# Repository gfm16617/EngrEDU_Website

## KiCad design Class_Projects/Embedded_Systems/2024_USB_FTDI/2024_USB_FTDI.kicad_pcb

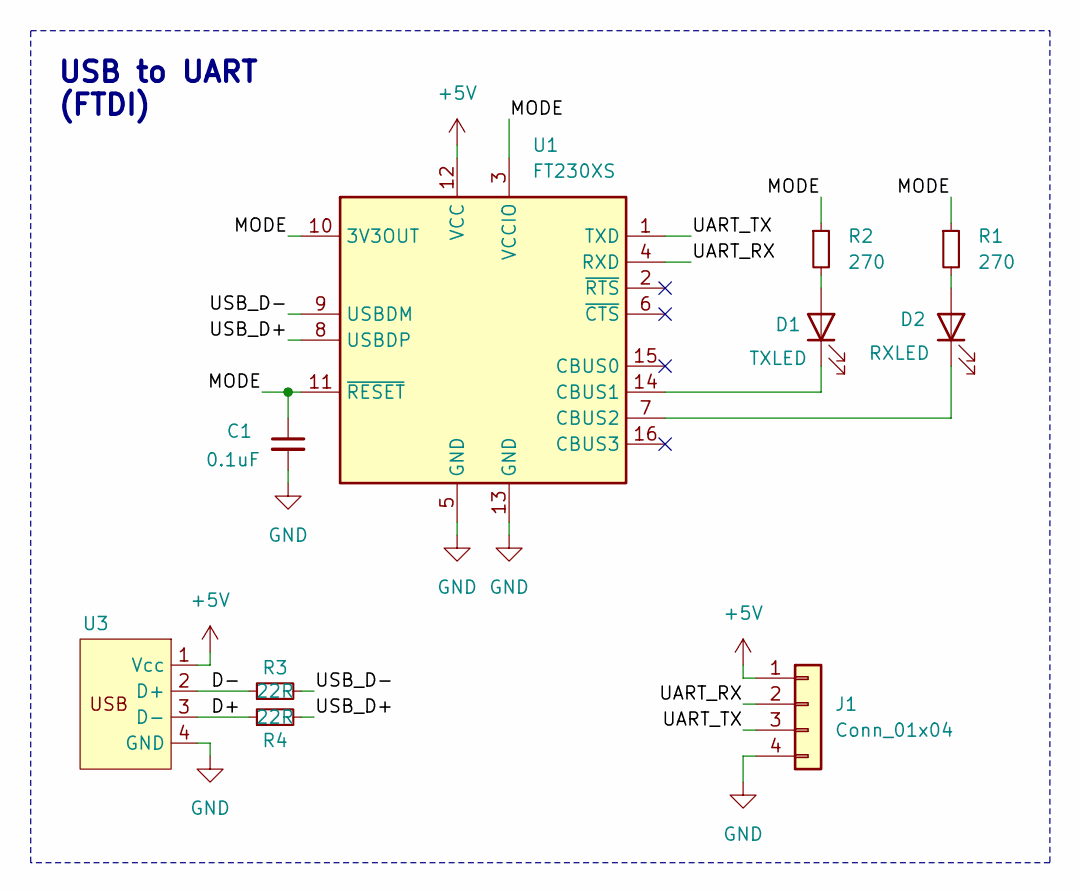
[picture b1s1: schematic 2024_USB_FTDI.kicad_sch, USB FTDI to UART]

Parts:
C1: 0.1uF; C_0805_2012Metric_Pad1.18x1.45mm_HandSolder
D1: TXLED; LED_0805_2012Metric_Pad1.15x1.40mm_HandSolder
D2: RXLED; LED_0805_2012Metric_Pad1.15x1.40mm_HandSolder
J1: Conn_01x04; PinHeader_1x04_P2.54mm_Vertical
R1, R2: 270; R_0805_2012Metric_Pad1.20x1.40mm_HandSolder
R3, R4: 22R; R_0805_2012Metric_Pad1.20x1.40mm_HandSolder
U1: FT230XS; SSOP-16_3.9x4.9mm_P0.635mm
U3: USB_PCB_Connector_SMD

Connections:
+5V: J1.1, U1.12 (VCC), U3.1 (Vcc)
/D+: R4.1, U3.3 (D-)
/D-: R3.1, U3.2 (D+)
/MODE: C1.1, R1.1, R2.1, U1.3 (VCCIO), U1.10 (3V3OUT), U1.11 (~RESET)
/UART_RX: J1.2, U1.4 (RXD)
/UART_TX: J1.3, U1.1 (TXD)
/USB_D+: R4.2, U1.8 (USBDP)
/USB_D-: R3.2, U1.9 (USBDM)
GND: C1.2, J1.4, U1.5 (GND), U1.13 (GND), U3.4 (GND)
unnamed: D1.2 (A), R2.2
unnamed: D1.1 (K), U1.14 (CBUS1)
unnamed: D2.2 (A), R1.2
unnamed: D2.1 (K), U1.7 (CBUS2)

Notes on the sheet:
USB to UART (FTDI)

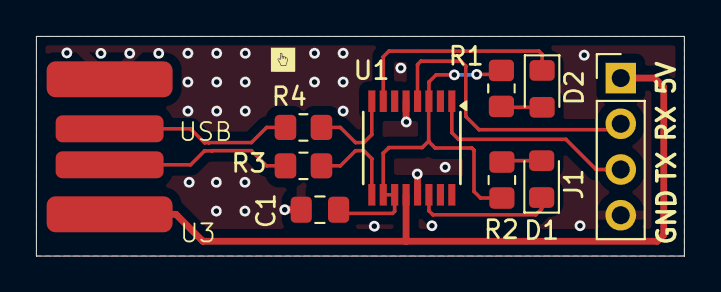
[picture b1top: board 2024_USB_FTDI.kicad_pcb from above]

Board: 2 copper layers, 36.0 x 12.2 mm, 10 parts (0 on the bottom side), 13 nets.

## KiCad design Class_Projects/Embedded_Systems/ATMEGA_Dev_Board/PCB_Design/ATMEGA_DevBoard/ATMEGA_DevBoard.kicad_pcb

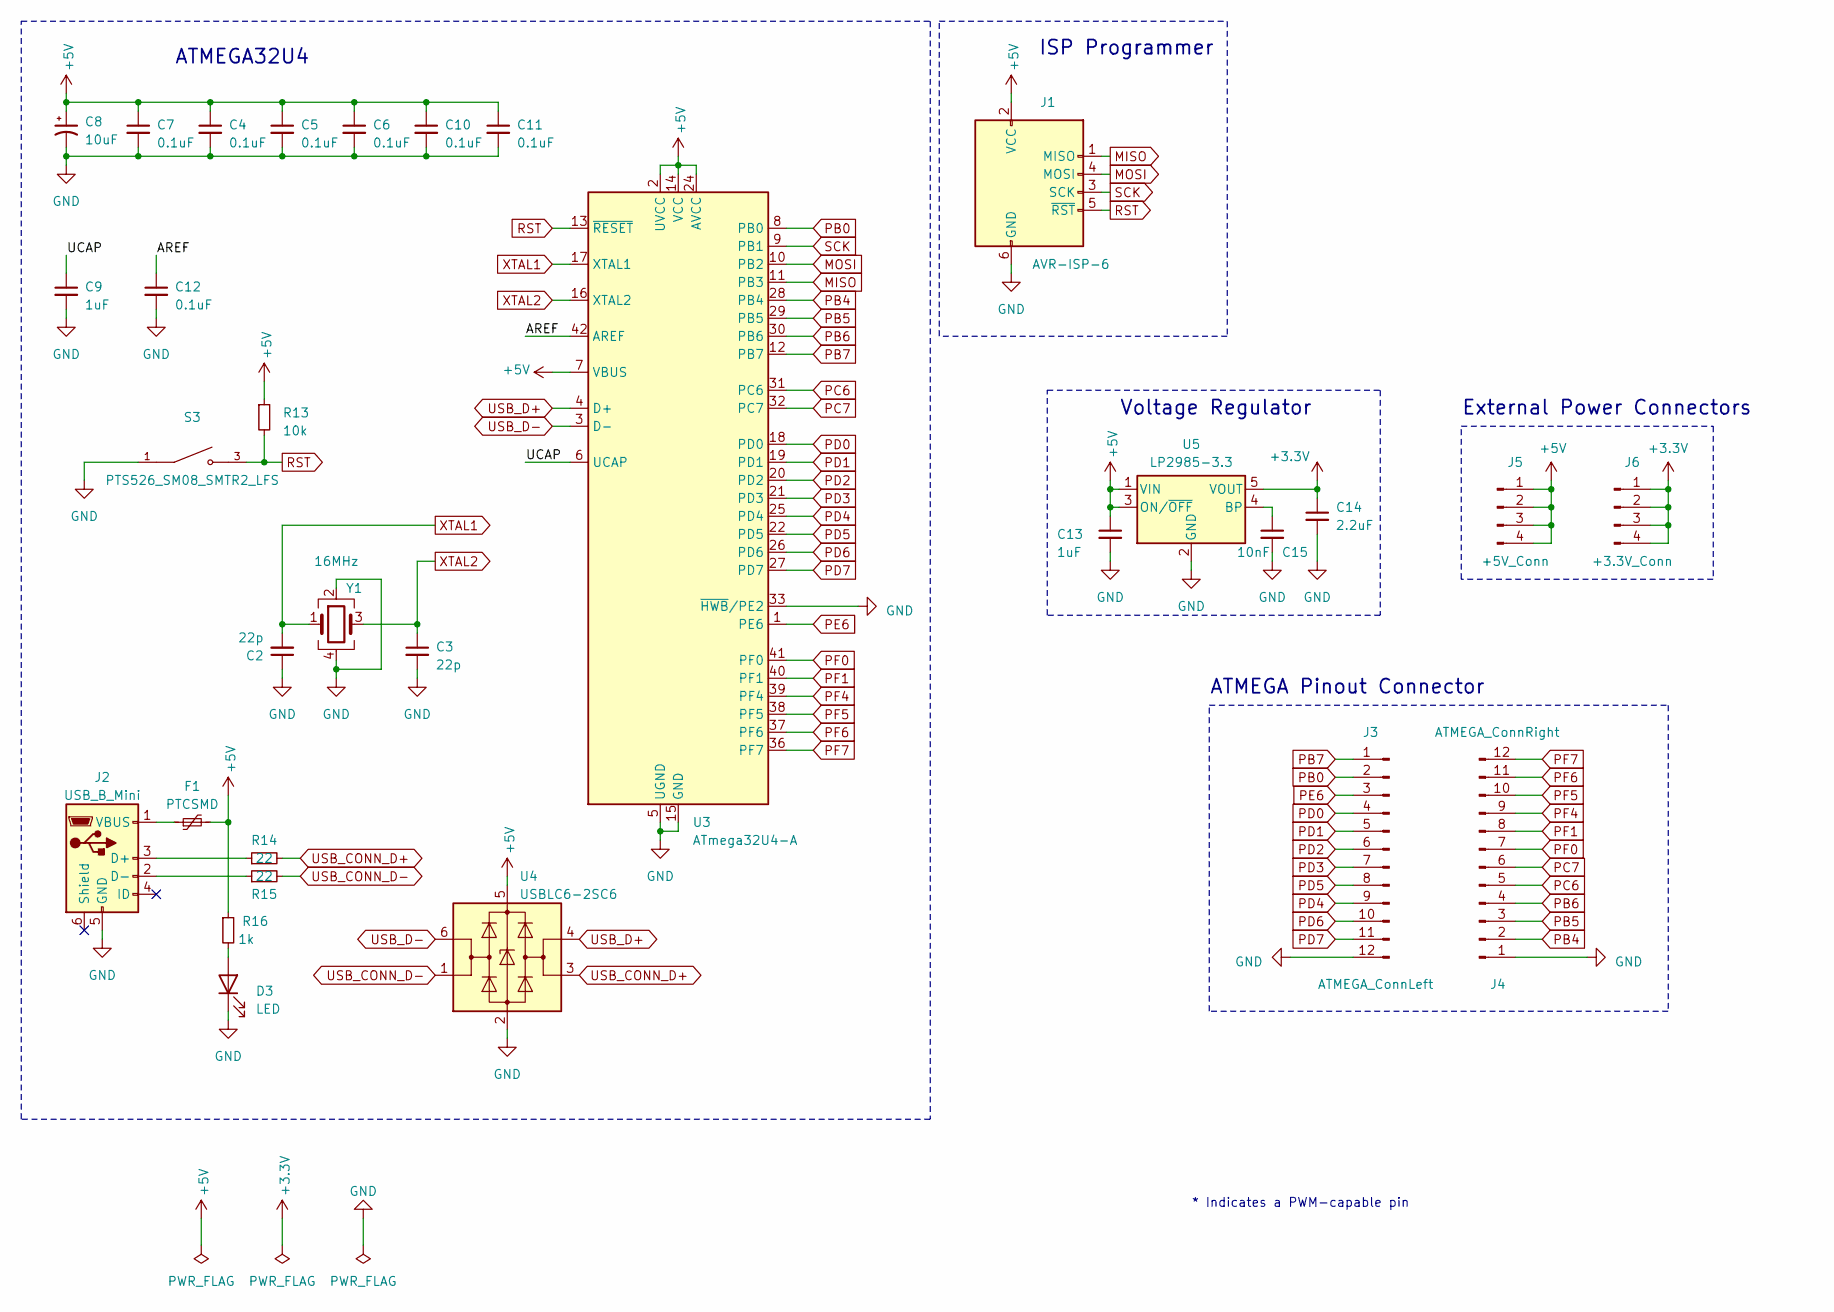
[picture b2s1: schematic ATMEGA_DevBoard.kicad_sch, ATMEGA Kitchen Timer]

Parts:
C2, C3: 22p; C_0603_1608Metric
C4, C5, C6, C7, C10, C11, C12: 0.1uF; C_0603_1608Metric
C8: 10uF; C_0805_2012Metric
C9, C13: 1uF; C_0603_1608Metric
C14: 2.2uF; C_0603_1608Metric
C15: 10nF; C_0603_1608Metric
D3: LED; LED_0805_2012Metric
F1: PTCSMD; Fuse_1812_4532Metric
J1: AVR-ISP-6; PinSocket_2x03_P2.54mm_Vertical
J2: USB_B_Mini; USB_Mini-B_Lumberg_2486_01_Horizontal
J3: ATMEGA_ConnLeft; PinHeader_1x12_P2.54mm_Vertical
J4: ATMEGA_ConnRight; PinHeader_1x12_P2.54mm_Vertical
J5: +5V_Conn; PinHeader_1x04_P2.54mm_Vertical
J6: +3.3V_Conn; PinHeader_1x04_P2.54mm_Vertical
R13: 10k; R_0603_1608Metric
R14, R15: 22; R_0603_1608Metric
R16: 1k; R_0603_1608Metric
S3: PTS526_SM08_SMTR2_LFS; PTS526_SMD_Button; PARTREV 20 mar 19
U3: ATmega32U4-A; TQFP-44_10x10mm_P0.8mm
U4: USBLC6-2SC6; SOT-23-6
U5: LP2985-3.3; SOT-23-5
Y1: 16MHz; Crystal_SMD_Abracon_ABM8G-4Pin_3.2x2.5mm

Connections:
+3.3V: C14.1, J6.1, J6.2, J6.3, J6.4, U5.5 (VOUT)
+5V: C4.1, C5.1, C6.1, C7.1, C8.1, C10.1, C11.1, C13.1, F1.2, J1.2 (VCC), J5.1, J5.2, J5.3, J5.4, R13.1, R16.1, U3.2 (UVCC), U3.7 (VBUS), U3.14 (VCC), U3.24 (AVCC), U3.34 (VCC), U3.44 (AVCC), U4.5 (VBUS), U5.1 (VIN), U5.3 (ON/~OFF)
/AREF: C12.1, U3.42 (AREF)
/UCAP: C9.1, U3.6 (UCAP)
GND: C2.1, C3.2, C4.2, C5.2, C6.2, C7.2, C8.2, C9.2, C10.2, C11.2, C12.2, C13.2, C14.2, C15.2, D3.1 (K), J1.6 (GND), J2.5 (GND), J3.12, J4.1, S3.1, U3.5 (UGND), U3.15 (GND), U3.23 (GND), U3.33 (~HWB/PE2), U3.35 (GND), U3.43 (GND), U4.2 (GND), U5.2 (GND), Y1.2, Y1.4
MISO: J1.1 (MISO), U3.11 (PB3)
MOSI: J1.4 (MOSI), U3.10 (PB2)
unnamed: D3.2 (A), R16.2
unnamed: J2.3 (D+), R14.1
unnamed: J2.2 (D-), R15.1
unnamed: F1.1, J2.1 (VBUS)
unnamed: C15.1, U5.4 (BP)
PB0: J3.2, U3.8 (PB0)
PB4: J4.2, U3.28 (PB4)
PB5: J4.3, U3.29 (PB5)
PB6: J4.4, U3.30 (PB6)
PB7: J3.1, U3.12 (PB7)
PC6: J4.5, U3.31 (PC6)
PC7: J4.6, U3.32 (PC7)
PD0: J3.4, U3.18 (PD0)
PD1: J3.5, U3.19 (PD1)
PD2: J3.6, U3.20 (PD2)
PD3: J3.7, U3.21 (PD3)
PD4: J3.9, U3.25 (PD4)
PD5: J3.8, U3.22 (PD5)
PD6: J3.10, U3.26 (PD6)
PD7: J3.11, U3.27 (PD7)
PE6: J3.3, U3.1 (PE6)
PF0: J4.7, U3.41 (PF0)
PF1: J4.8, U3.40 (PF1)
PF4: J4.9, U3.39 (PF4)
PF5: J4.10, U3.38 (PF5)
PF6: J4.11, U3.37 (PF6)
PF7: J4.12, U3.36 (PF7)
RST: J1.5 (~RST), R13.2, S3.3, U3.13 (~RESET)
SCK: J1.3 (SCK), U3.9 (PB1)
USB_CONN_D+: R14.2, U4.3 (I/O2)
USB_CONN_D-: R15.2, U4.1 (I/O1)
USB_D+: U3.4 (D+), U4.4 (I/O2)
USB_D-: U3.3 (D-), U4.6 (I/O1)
XTAL1: C2.2, U3.17 (XTAL1), Y1.1
XTAL2: C3.1, U3.16 (XTAL2), Y1.3

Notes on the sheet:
External Power Connectors
Voltage Regulator
ATMEGA32U4
* Indicates a PWM-capable pin
ISP Programmer
ATMEGA Pinout Connector

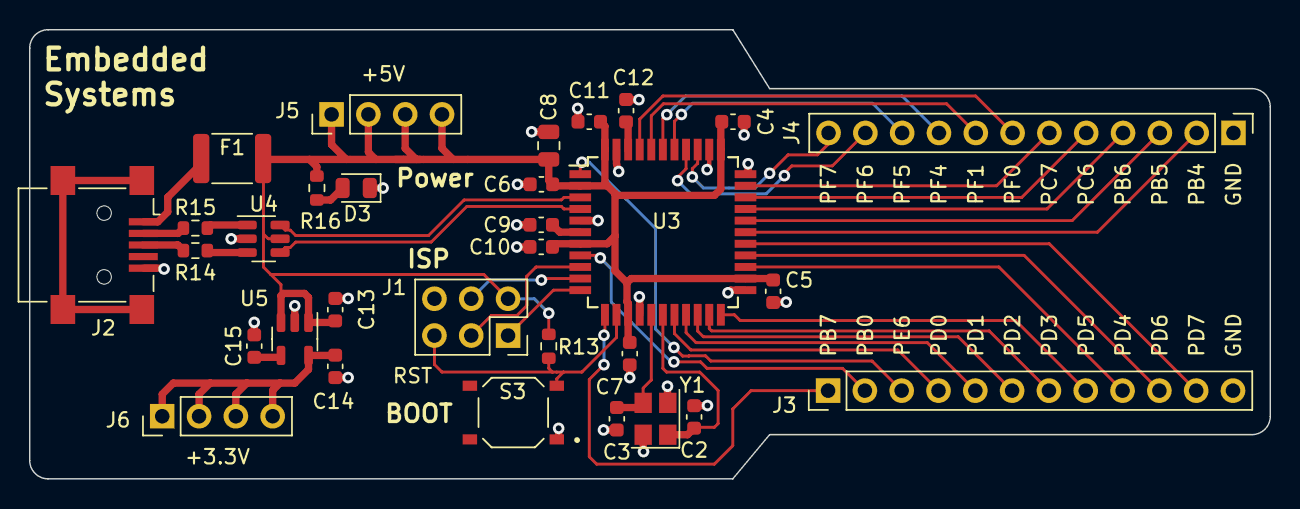
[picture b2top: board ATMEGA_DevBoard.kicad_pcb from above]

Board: 2 copper layers, 85.6 x 31.0 mm, 31 parts (0 on the bottom side), 42 nets.

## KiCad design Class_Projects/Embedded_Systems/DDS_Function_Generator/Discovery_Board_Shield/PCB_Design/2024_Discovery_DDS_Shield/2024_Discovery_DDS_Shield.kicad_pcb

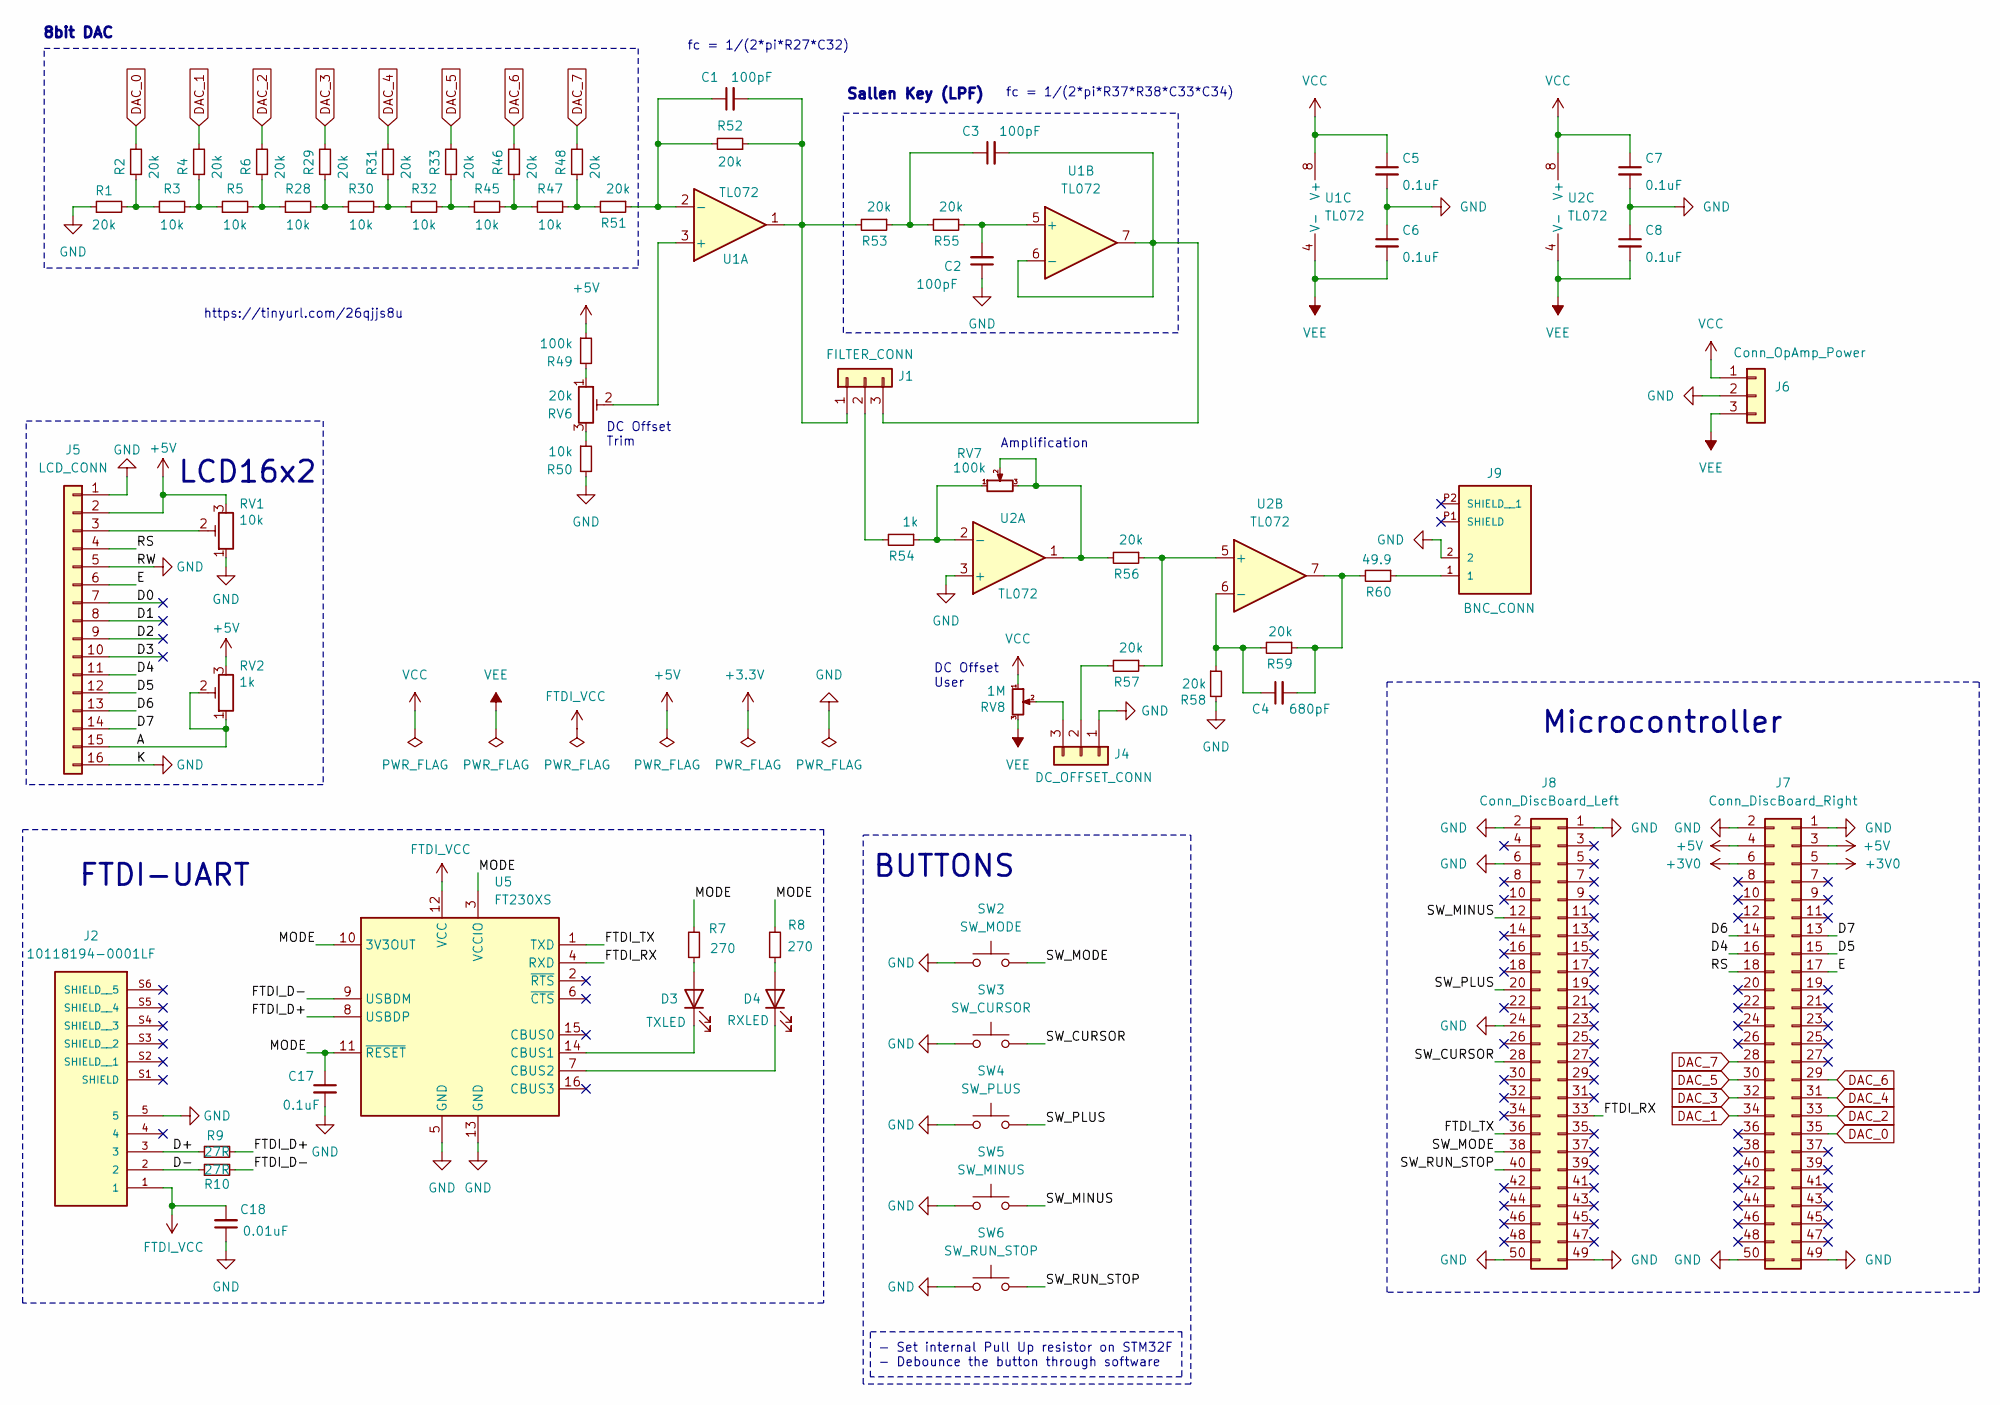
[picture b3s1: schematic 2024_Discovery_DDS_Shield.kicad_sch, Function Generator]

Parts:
C1, C2, C3: 100pF; C_0805_2012Metric_Pad1.18x1.45mm_HandSolder
C4: 680pF; C_0805_2012Metric_Pad1.18x1.45mm_HandSolder
C5, C6, C7, C8, C17: 0.1uF; C_0805_2012Metric_Pad1.18x1.45mm_HandSolder
C18: 0.01uF; C_0805_2012Metric_Pad1.18x1.45mm_HandSolder
D3: TXLED; LED_0805_2012Metric_Pad1.15x1.40mm_HandSolder
D4: RXLED; LED_0805_2012Metric_Pad1.15x1.40mm_HandSolder
J1: FILTER_CONN; PinSocket_1x03_P2.54mm_Vertical
J2: 10118194-0001LF; AMPHENOL_10118194-0001LF; PARTREV D
J4: DC_OFFSET_CONN; PinSocket_1x03_P2.54mm_Vertical
J5: LCD_CONN; PinSocket_1x16_P2.54mm_Vertical
J6: Conn_OpAmp_Power; PinHeader_1x03_P2.54mm_Vertical
J7: Conn_DiscBoard_Right; PinSocket_2x25_P2.54mm_Vertical
J8: Conn_DiscBoard_Left; PinSocket_2x25_P2.54mm_Vertical
J9: BNC_CONN; BNC_RightAngle_50ohm
R1, R2, R4, R6, R29, R31, R33, R46, R48, R51, R52, R53, R55, R56, R57, R58, R59: 20k; R_0805_2012Metric_Pad1.20x1.40mm_HandSolder
R3, R5, R28, R30, R32, R45, R47, R50: 10k; R_0805_2012Metric_Pad1.20x1.40mm_HandSolder
R7, R8: 270; R_0805_2012Metric_Pad1.20x1.40mm_HandSolder
R9, R10: 27R; R_0805_2012Metric_Pad1.20x1.40mm_HandSolder
R49: 100k; R_0805_2012Metric_Pad1.20x1.40mm_HandSolder
R54: 1k; R_0805_2012Metric_Pad1.20x1.40mm_HandSolder
R60: 49.9; R_0805_2012Metric_Pad1.20x1.40mm_HandSolder
RV1: 10k; Potentiometer_Bourns_3296W_Vertical
RV2: 1k; Potentiometer_Bourns_3296W_Vertical
RV6: 20k; Potentiometer_Bourns_3296W_Vertical
RV7: 100k; Potentiometer_Alps_RK09K_Single_Vertical
RV8: 1M; Potentiometer_Alps_RK09K_Single_Vertical
SW2: SW_MODE; SW_PUSH_6mm_H5mm
SW3: SW_CURSOR; SW_PUSH_6mm_H5mm
SW4: SW_PLUS; SW_PUSH_6mm_H5mm
SW5: SW_MINUS; SW_PUSH_6mm_H5mm
SW6: SW_RUN_STOP; SW_PUSH_6mm_H5mm
U1, U2: TL072; SOIC-8_3.9x4.9mm_P1.27mm
U5: FT230XS; SSOP-16_3.9x4.9mm_P0.635mm

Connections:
+3V0: J7.5, J7.6
+5V: J5.2, J7.3, J7.4, R49.1, RV1.3, RV2.3
/A: J5.15, RV2.1, RV2.2
/D0: J5.7
/D1: J5.8
/D2: J5.9
/D3: J5.10
/D4: J5.11, J7.16
/D5: J5.12, J7.15
/D6: J5.13, J7.14
/D7: J5.14, J7.13
/D+: J2.3, R9.1
/D-: J2.2, R10.1
/E: J5.6, J7.17
/FTDI_D+: R9.2, U5.8 (USBDP)
/FTDI_D-: R10.2, U5.9 (USBDM)
/FTDI_RX: J8.33, U5.4 (RXD)
/FTDI_TX: J8.36, U5.1 (TXD)
/MODE: C17.1, R7.2, R8.2, U5.3 (VCCIO), U5.10 (3V3OUT), U5.11 (~RESET)
/RS: J5.4, J7.18
/SW_CURSOR: J8.28, SW3.2
/SW_MINUS: J8.12, SW5.2
/SW_MODE: J8.38, SW2.2
/SW_PLUS: J8.20, SW4.2
/SW_RUN_STOP: J8.40, SW6.2
DAC_0: J7.35, R2.2
DAC_1: J7.34, R4.2
DAC_2: J7.33, R6.2
DAC_3: J7.32, R29.2
DAC_4: J7.31, R31.2
DAC_5: J7.30, R33.2
DAC_6: J7.29, R46.2
DAC_7: J7.28, R48.2
FTDI_VCC: C18.2, J2.1, U5.12 (VCC)
GND: C2.1, C5.2, C6.1, C7.2, C8.1, C17.2, C18.1, J2.5, J4.1, J5.1, J5.5, J5.16, J6.2, J7.1, J7.2, J7.49, J7.50, J8.1, J8.2, J8.6, J8.24, J8.49, J8.50, J9.2, R1.1, R50.2, R58.2, RV1.1, SW2.1, SW3.1, SW4.1, SW5.1, SW6.1, U2.3 (+), U5.5 (GND), U5.13 (GND)
unnamed: C3.1, R53.1, R55.2
unnamed: C4.2, R59.1, R60.2, U2.7
unnamed: D3.2 (A), R7.1
unnamed: D3.1 (K), U5.14 (CBUS1)
unnamed: D4.2 (A), R8.1
unnamed: D4.1 (K), U5.7 (CBUS2)
unnamed: C1.2, J1.1, R52.1, R53.2, U1.1
unnamed: J1.2, R54.2
unnamed: C3.2, J1.3, U1.6 (-), U1.7
unnamed: J4.2, R57.2
unnamed: J4.3, RV8.2
unnamed: J5.3, RV1.2
unnamed: J9.1, R60.1
unnamed: R1.2, R2.1, R3.1
unnamed: R3.2, R4.1, R5.1
unnamed: R5.2, R6.1, R28.1
unnamed: R28.2, R29.1, R30.1
unnamed: R30.2, R31.1, R32.1
unnamed: R32.2, R33.1, R45.1
unnamed: R45.2, R46.1, R47.2
unnamed: R47.1, R48.1, R51.2
unnamed: R49.2, RV6.1
unnamed: R50.1, RV6.3
unnamed: R56.2, RV7.2, RV7.3, U2.1
unnamed: RV6.2, U1.3 (+)
unnamed: C1.1, R51.1, R52.2, U1.2 (-)
unnamed: C2.2, R55.1, U1.5 (+)
unnamed: R54.1, RV7.1, U2.2 (-)
unnamed: R56.1, R57.1, U2.5 (+)
unnamed: C4.1, R58.1, R59.2, U2.6 (-)
VCC: C5.1, C7.1, J6.1, RV8.1, U1.8 (V+), U2.8 (V+)
VEE: C6.2, C8.2, J6.3, RV8.3, U1.4 (V-), U2.4 (V-)

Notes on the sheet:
- Set internal Pull Up resistor on STM32F - Debounce the button through software
Microcontroller
fc = 1/(2*pi*R37*R38*C33*C34)
BUTTONS
fc = 1/(2*pi*R27*C32)
8bit DAC
https://tinyurl.com/26qjjs8u
Amplification
DC Offset Trim
DC Offset User
LCD16x2
Sallen Key (LPF)
FTDI-UART

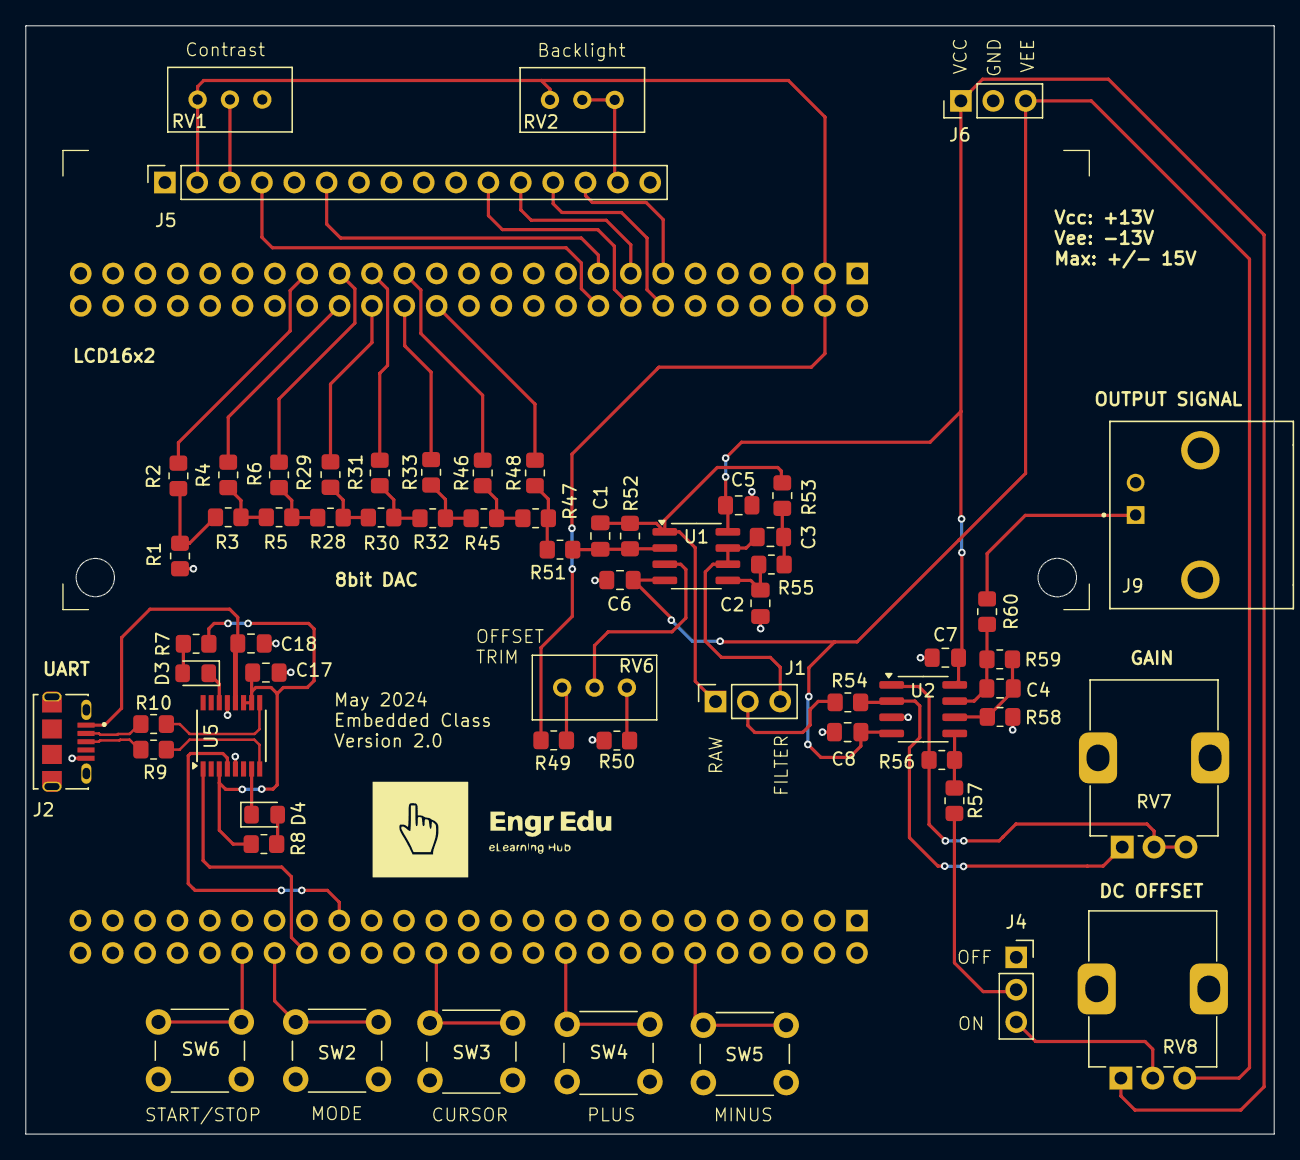
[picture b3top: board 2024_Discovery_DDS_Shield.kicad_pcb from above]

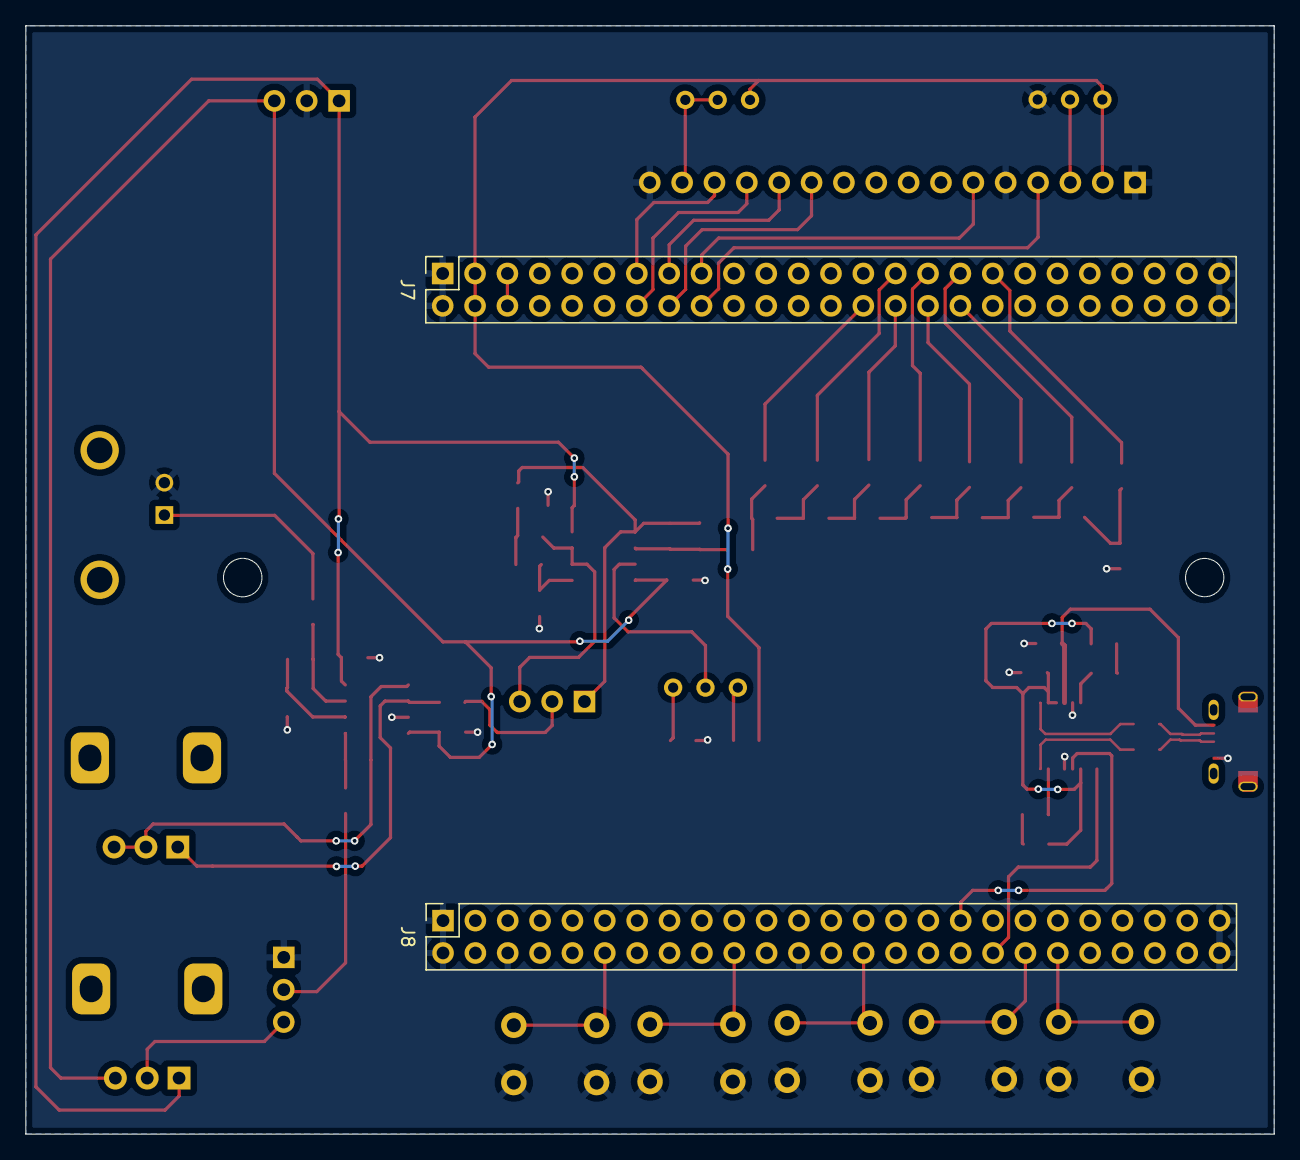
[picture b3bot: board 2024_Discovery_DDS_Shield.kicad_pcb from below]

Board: 2 copper layers, 98.0 x 87.0 mm, 65 parts (2 on the bottom side), 63 nets.

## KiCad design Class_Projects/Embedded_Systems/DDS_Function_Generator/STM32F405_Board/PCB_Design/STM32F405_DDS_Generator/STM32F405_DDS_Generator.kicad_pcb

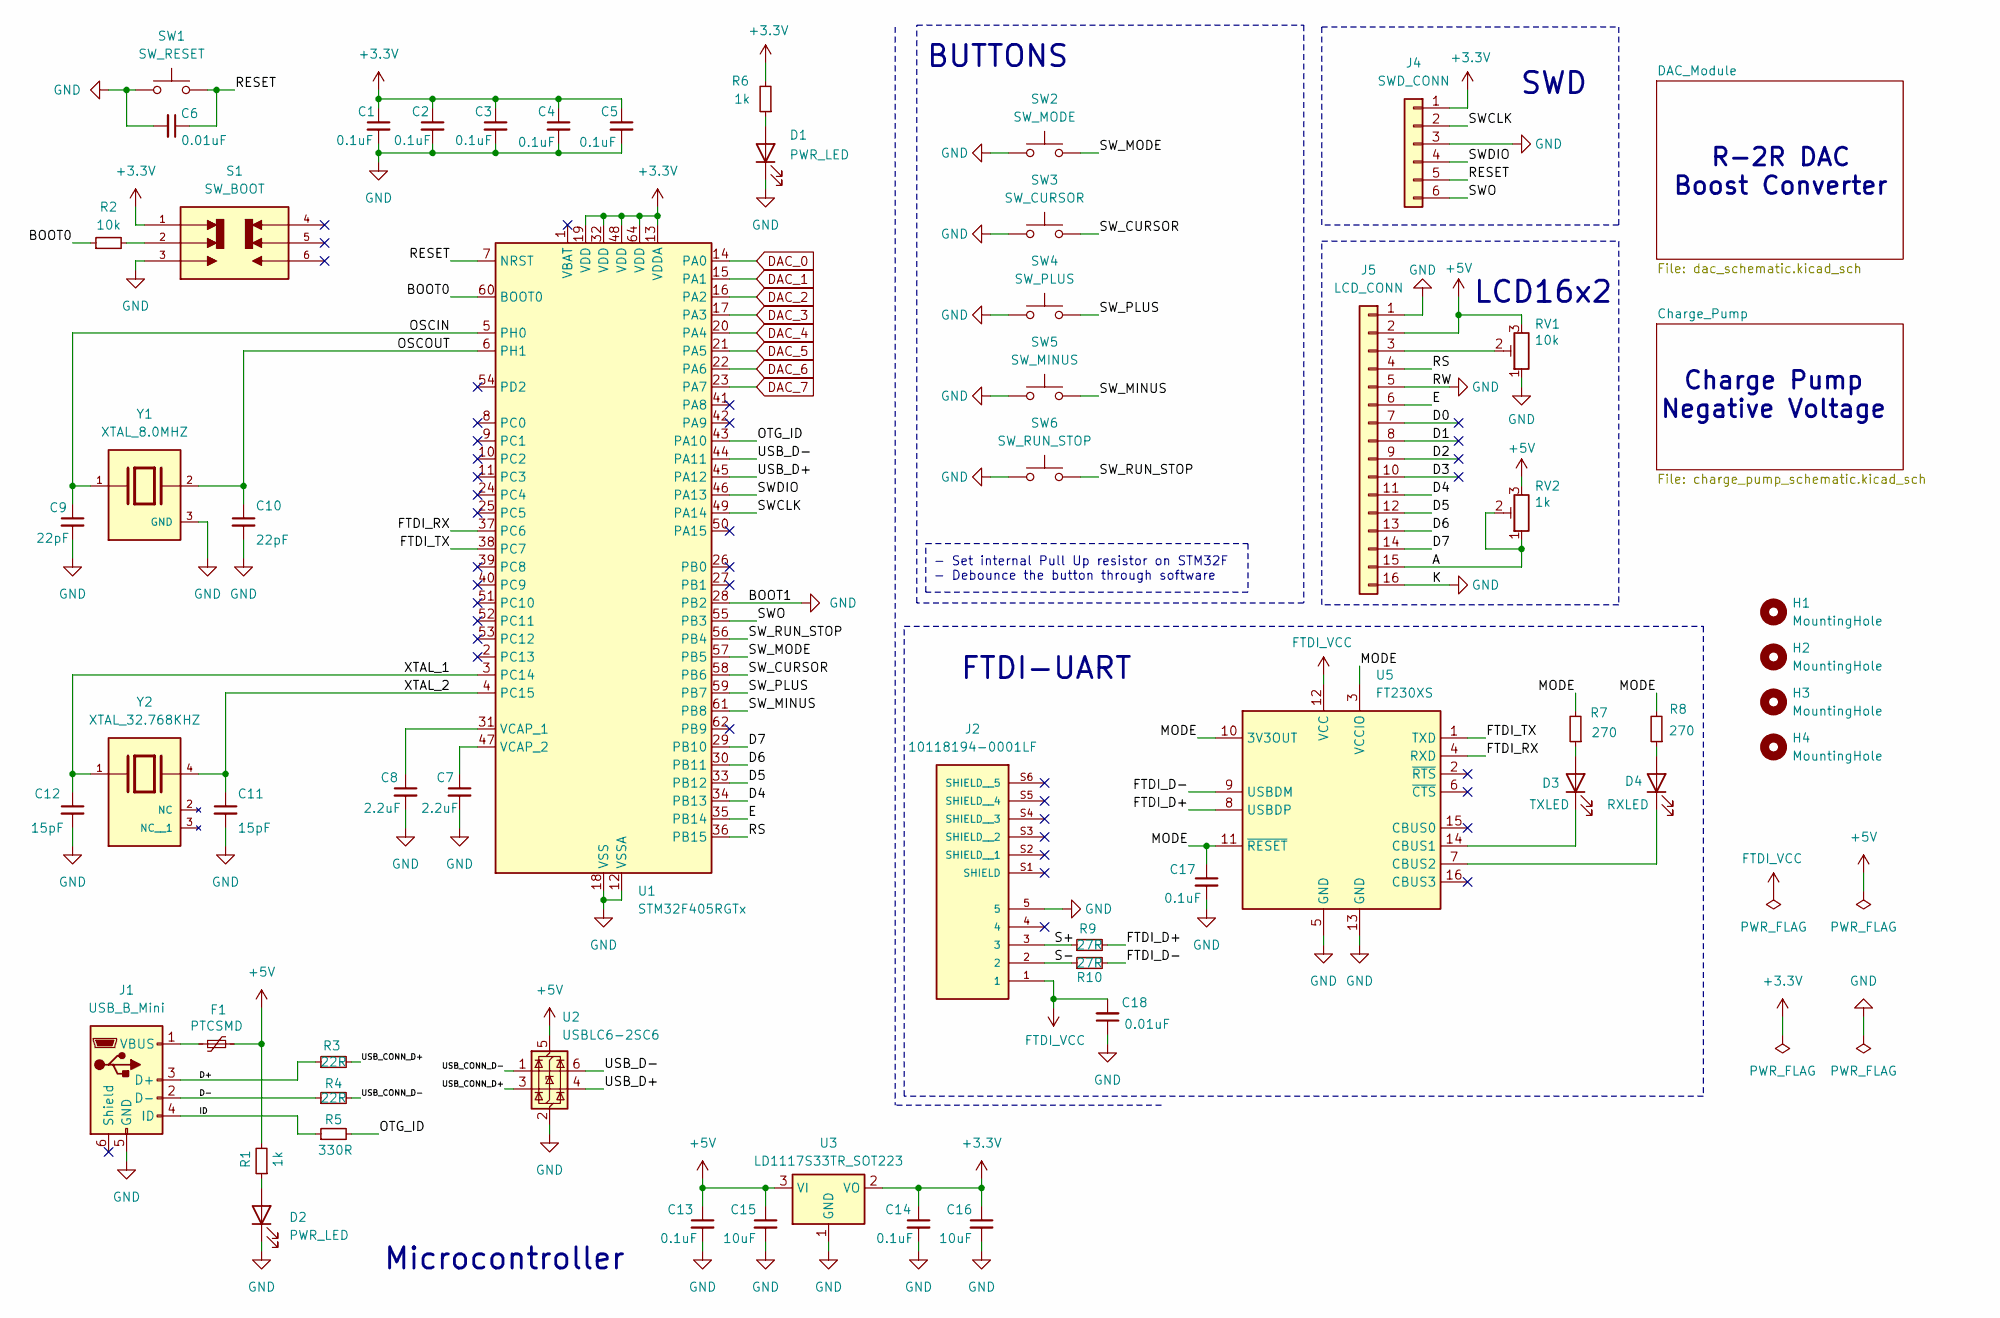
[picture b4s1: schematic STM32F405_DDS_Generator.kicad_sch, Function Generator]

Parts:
C1, C2, C3, C4, C5, C13, C14, C17: 0.1uF; C_0805_2012Metric_Pad1.18x1.45mm_HandSolder
C6, C18: 0.01uF; C_0805_2012Metric_Pad1.18x1.45mm_HandSolder
C7, C8: 2.2uF; C_0805_2012Metric_Pad1.18x1.45mm_HandSolder
C9, C10: 22pF; C_0805_2012Metric_Pad1.18x1.45mm_HandSolder
C11, C12: 15pF; C_0805_2012Metric_Pad1.18x1.45mm_HandSolder
C15, C16: 10uF; C_0805_2012Metric_Pad1.18x1.45mm_HandSolder
D1, D2: PWR_LED; LED_0805_2012Metric_Pad1.15x1.40mm_HandSolder
D3: TXLED; LED_0805_2012Metric_Pad1.15x1.40mm_HandSolder
D4: RXLED; LED_0805_2012Metric_Pad1.15x1.40mm_HandSolder
F1: PTCSMD; Fuse_1812_4532Metric
H1, H2, H3, H4: MountingHole; MountingHole_3.2mm_M3_Pad_Via
J1: USB_B_Mini; USB_Mini-B_Wuerth_65100516121_Horizontal
J2: 10118194-0001LF; AMPHENOL_10118194-0001LF; PARTREV D
J4: SWD_CONN; PinHeader_1x06_P2.54mm_Vertical
J5: LCD_CONN; PinSocket_1x16_P2.54mm_Vertical
R1, R6: 1k; R_0805_2012Metric_Pad1.20x1.40mm_HandSolder
R2: 10k; R_0805_2012Metric_Pad1.20x1.40mm_HandSolder
R3, R4: 22R; R_0805_2012Metric_Pad1.20x1.40mm_HandSolder
R5: 330R; R_0805_2012Metric_Pad1.20x1.40mm_HandSolder
R7, R8: 270; R_0805_2012Metric_Pad1.20x1.40mm_HandSolder
R9, R10: 27R; R_0805_2012Metric_Pad1.20x1.40mm_HandSolder
RV1: 10k; Potentiometer_Bourns_3296W_Vertical
RV2: 1k; Potentiometer_Bourns_3296W_Vertical
S1: SW_BOOT; SW_JS202011SCQN; PARTREV 26 May 22
SW1: SW_RESET; PTS636SM25FSMTRLFS
SW2: SW_MODE; SW_PUSH_6mm_H5mm
SW3: SW_CURSOR; SW_PUSH_6mm_H5mm
SW4: SW_PLUS; SW_PUSH_6mm_H5mm
SW5: SW_MINUS; SW_PUSH_6mm_H5mm
SW6: SW_RUN_STOP; SW_PUSH_6mm_H5mm
U1: STM32F405RGTx; LQFP-64_10x10mm_P0.5mm
U2: USBLC6-2SC6; SOT-23-6
U3: LD1117S33TR_SOT223; SOT-223-3_TabPin2
U5: FT230XS; SSOP-16_3.9x4.9mm_P0.635mm
Y1: XTAL_8.0MHZ; XTAL_ABLSG-8.000MHZ-D-2-Y-T; PARTREV 08.20.10
Y2: XTAL_32.768KHZ; XTAL_ABS25-32.768KHZ-1-T; PARTREV 43738

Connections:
+3.3V: C1.1, C2.1, C3.1, C4.1, C5.1, C14.1, C16.1, J4.1, R6.2, S1.1, U1.13 (VDDA), U1.19 (VDD), U1.32 (VDD), U1.48 (VDD), U1.64 (VDD), U3.2 (VO)
+5V: C13.1, C15.1, F1.2, J5.2, R1.2, RV1.3, RV2.3, U2.5 (VBUS), U3.3 (VI); also elsewhere on the board
/A: J5.15, RV2.1, RV2.2
/BOOT0: R2.1, U1.60 (BOOT0)
/D0: J5.7
/D1: J5.8
/D2: J5.9
/D3: J5.10
/D4: J5.11, U1.34 (PB13)
/D5: J5.12, U1.33 (PB12)
/D6: J5.13, U1.30 (PB11)
/D7: J5.14, U1.29 (PB10)
/D+: J1.3 (D+), R3.1
/D-: J1.2 (D-), R4.1
/E: J5.6, U1.35 (PB14)
/FTDI_D+: R9.2, U5.8 (USBDP)
/FTDI_D-: R10.2, U5.9 (USBDM)
/FTDI_RX: U1.37 (PC6), U5.4 (RXD)
/FTDI_TX: U1.38 (PC7), U5.1 (TXD)
/ID: J1.4 (ID), R5.1
/MODE: C17.1, R7.2, R8.2, U5.3 (VCCIO), U5.10 (3V3OUT), U5.11 (~RESET)
/OSCIN: C9.1, U1.5 (PH0), Y1.1
/OSCOUT: C10.1, U1.6 (PH1), Y1.2
/OTG_ID: R5.2, U1.43 (PA10)
/RESET: C6.1, J4.5, SW1.2, U1.7 (NRST)
/RS: J5.4, U1.36 (PB15)
/S+: J2.3, R9.1
/S-: J2.2, R10.1
/SWCLK: J4.2, U1.49 (PA14)
/SWDIO: J4.4, U1.46 (PA13)
/SWO: J4.6, U1.55 (PB3)
/SW_CURSOR: SW3.2, U1.58 (PB6)
/SW_MINUS: SW5.2, U1.61 (PB8)
/SW_MODE: SW2.2, U1.57 (PB5)
/SW_PLUS: SW4.2, U1.59 (PB7)
/SW_RUN_STOP: SW6.2, U1.56 (PB4)
/USB_CONN_D+: R3.2, U2.3 (I/O2)
/USB_CONN_D-: R4.2, U2.1 (I/O1)
/USB_D+: U1.45 (PA12), U2.4 (I/O2)
/USB_D-: U1.44 (PA11), U2.6 (I/O1)
/XTAL_1: C12.1, U1.3 (PC14), Y2.1
/XTAL_2: C11.1, U1.4 (PC15), Y2.4
DAC_0: U1.14 (PA0); also elsewhere on the board
DAC_1: U1.15 (PA1); also elsewhere on the board
DAC_2: U1.16 (PA2); also elsewhere on the board
DAC_3: U1.17 (PA3); also elsewhere on the board
DAC_4: U1.20 (PA4); also elsewhere on the board
DAC_5: U1.21 (PA5); also elsewhere on the board
DAC_6: U1.22 (PA6); also elsewhere on the board
DAC_7: U1.23 (PA7); also elsewhere on the board
FTDI_VCC: C18.2, J2.1, U5.12 (VCC)
GND: C1.2, C2.2, C3.2, C4.2, C5.2, C6.2, C7.2, C8.2, C9.2, C10.2, C11.2, C12.2, C13.2, C14.2, C15.2, C16.2, C17.2, C18.1, D1.1 (K), D2.1 (K), J1.5 (GND), J2.5, J4.3, J5.1, J5.5, J5.16, RV1.1, S1.3, SW1.1, SW2.1, SW3.1, SW4.1, SW5.1, SW6.1, U1.12 (VSSA), U1.18 (VSS), U1.28 (PB2), U1.63 (VSS), U2.2 (GND), U3.1 (GND), U5.5 (GND), U5.13 (GND), Y1.3 (GND); also elsewhere on the board
unnamed: D1.2 (A), R6.1
unnamed: D2.2 (A), R1.1
unnamed: D3.2 (A), R7.1
unnamed: D3.1 (K), U5.14 (CBUS1)
unnamed: D4.2 (A), R8.1
unnamed: D4.1 (K), U5.7 (CBUS2)
unnamed: F1.1, J1.1 (VBUS)
unnamed: J5.3, RV1.2
unnamed: R2.2, S1.2
unnamed: C8.1, U1.31 (VCAP_1)
unnamed: C7.1, U1.47 (VCAP_2)

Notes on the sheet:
- Set internal Pull Up resistor on STM32F - Debounce the button through software
Microcontroller
BUTTONS
Charge Pump Negative Voltage
SWD
LCD16x2
R-2R DAC Boost Converter
FTDI-UART
